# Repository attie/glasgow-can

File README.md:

# Glasgow CAN Interface Addon

This repository provides the hardware and software components of a CAN Interface Add-On for the [Glasgow Digital Interface Explorer](https://github.com/GlasgowEmbedded/glasgow).

A rough spec is outlined below:

- Sits alongside a Glasgow board
- 2x CAN interfaces, available on a single port
- Standard DE-9 connectors
  - Default pinout is suitable for use with existing CAN and OBD-II adapter cables (on CAN1 and CAN2 repsectively)
  - Can be easily rewired by cutting jumpers
- Spring-loaded terminal blocks for ease-of-use
- Indicator LEDs for Tx and Rx
- Software configurable 120Ω termination, with state LED
- ESD protection
- CAN FD support in hardware (software to follow)

Future plans:

- Isolation between each CAN port and the Glasgow (and host)

Out-of-Tree support will be required when work on the applet begins (see PR [#213](https://github.com/GlasgowEmbedded/glasgow/pull/213)).

---

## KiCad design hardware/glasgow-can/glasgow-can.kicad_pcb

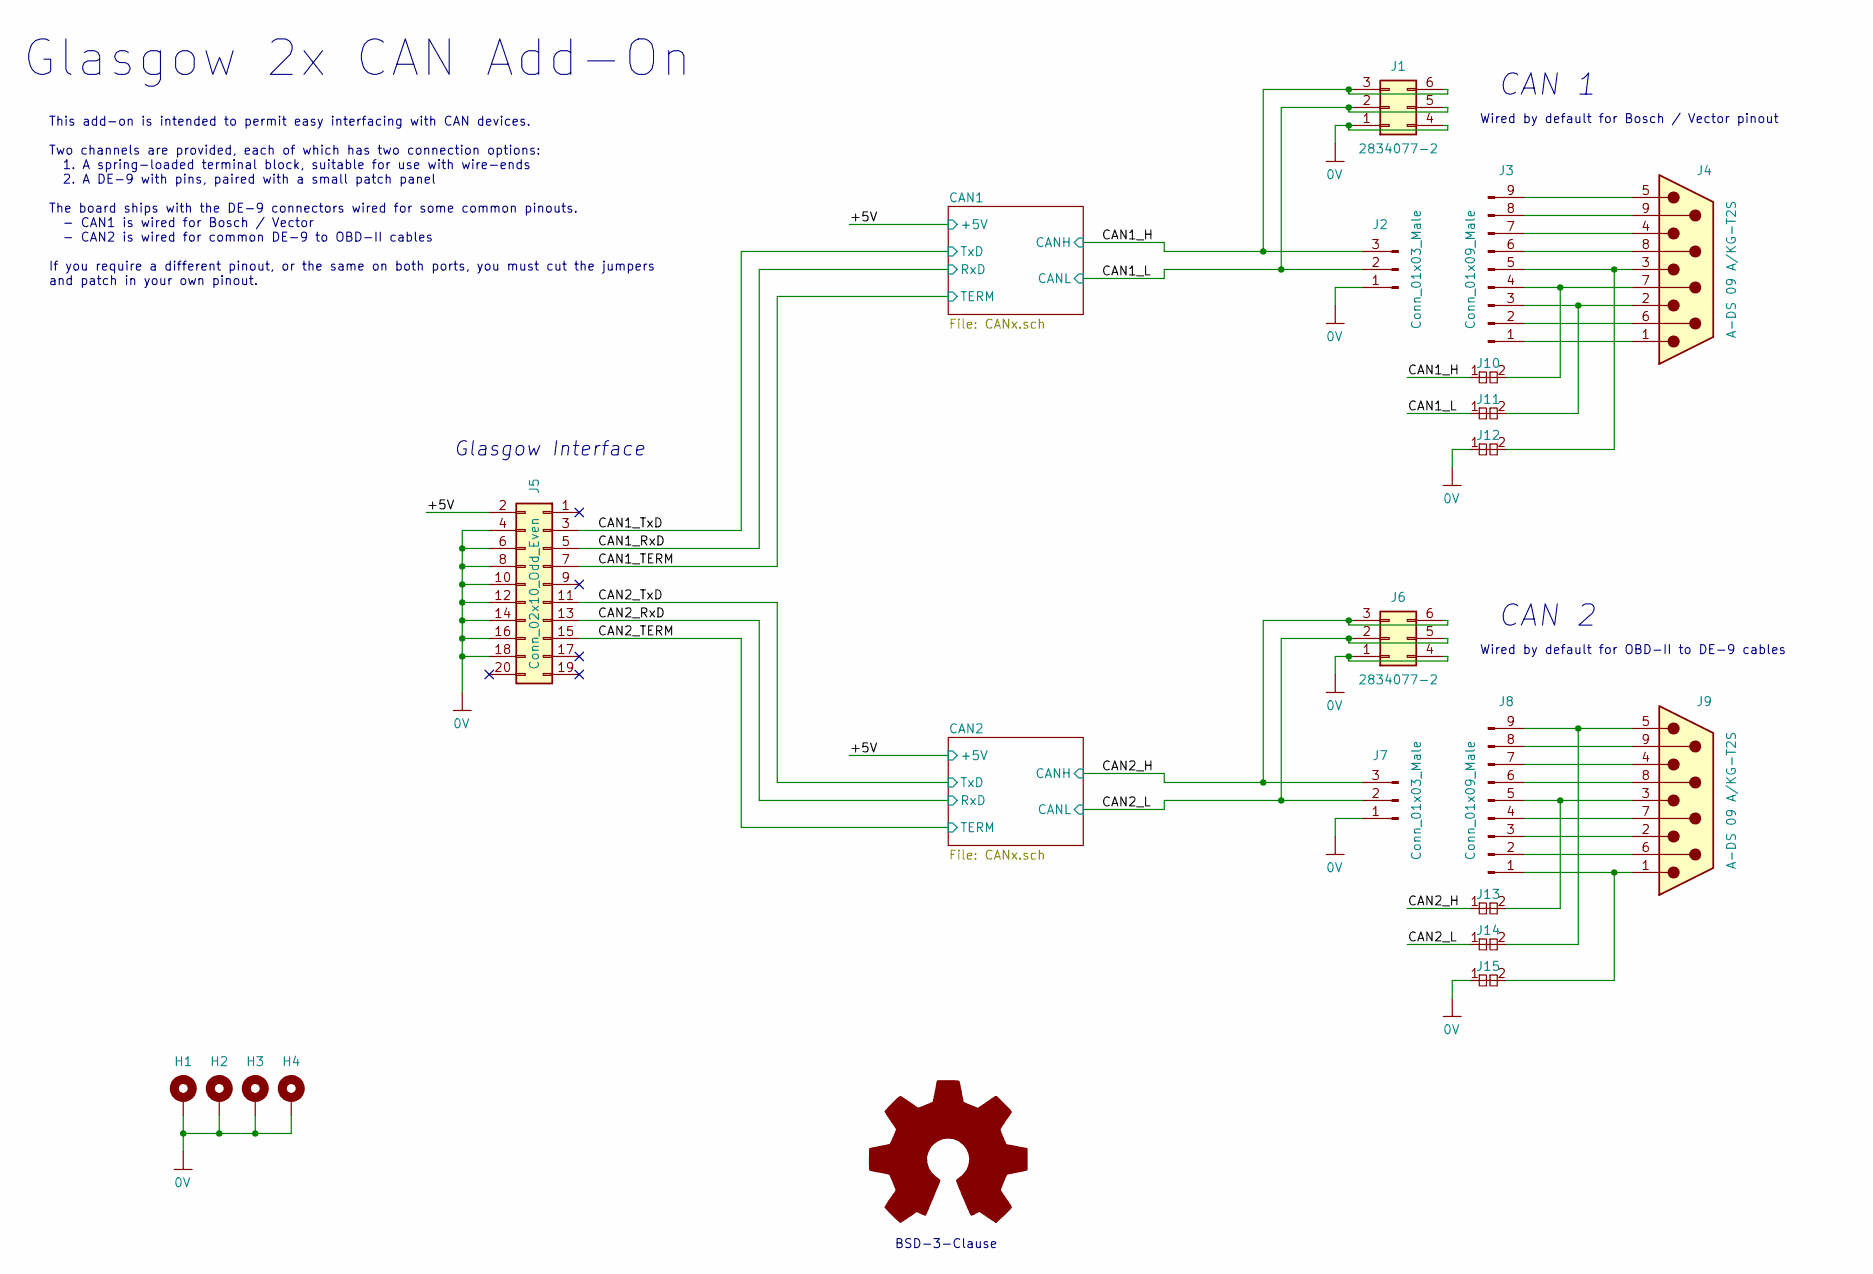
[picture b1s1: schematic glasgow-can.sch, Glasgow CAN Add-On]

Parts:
H1, H2, H3, H4: MountingHole_Pad; MountingHole_3.2mm_M3_Pad_Via
J1, J6: 2834077-2; TE_2834077-2; MPN 2834077-2
J2, J7: Conn_01x03_Male; PinHeader_1x03_P2.54mm_Vertical
J3, J8: Conn_01x09_Male; PinHeader_1x09_P2.54mm_Vertical
J4, J9: A-DS 09 A/KG-T2S; DSUB-9_Male_Horizontal_P2.77x2.84mm_EdgePinOffset7.70mm_Hou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; MPN A-DS 09 A/KG-T2S
J5: Conn_02x10_Odd_Even; IDC-Header_2x10_P2.54mm_Vertical
J10, J11, J12, J13, J14, J15: pkl_jumper_nc; J_NC_0603_20
LOGO1: Logo_Open_Hardware_Large; OSHW-Logo2_7.3x6mm_SilkScreen

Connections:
0V: H1.1, H2.1, H3.1, H4.1, J1.1, J1.4, J2.1, J5.4, J5.6, J5.8, J5.10, J5.12, J5.14, J5.16, J5.18, J6.1, J6.4, J7.1, J12.1, J15.1; also elsewhere on the board
/+5V: J5.2; also elsewhere on the board
/CAN1_H: J1.3, J1.6, J2.3, J10.1; also elsewhere on the board
/CAN1_L: J1.2, J1.5, J2.2, J11.1; also elsewhere on the board
/CAN1_RxD: J5.5; also elsewhere on the board
/CAN1_TERM: J5.7; also elsewhere on the board
/CAN1_TxD: J5.3; also elsewhere on the board
/CAN2_H: J6.3, J6.6, J7.3, J13.1; also elsewhere on the board
/CAN2_L: J6.2, J6.5, J7.2, J14.1; also elsewhere on the board
/CAN2_RxD: J5.13; also elsewhere on the board
/CAN2_TERM: J5.15; also elsewhere on the board
/CAN2_TxD: J5.11; also elsewhere on the board
unnamed: J3.1, J4.1
unnamed: J3.2, J4.6
unnamed: J3.6, J4.8
unnamed: J3.7, J4.4
unnamed: J3.8, J4.9
unnamed: J3.9, J4.5
unnamed: J8.2, J9.6
unnamed: J8.3, J9.2
unnamed: J8.4, J9.7
unnamed: J8.6, J9.8
unnamed: J8.7, J9.4
unnamed: J8.8, J9.9
unnamed: J3.4, J4.7, J10.2
unnamed: J3.3, J4.2, J11.2
unnamed: J3.5, J4.3, J12.2
unnamed: J8.5, J9.3, J13.2
unnamed: J8.9, J9.5, J14.2
unnamed: J8.1, J9.1, J15.2

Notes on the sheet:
Glasgow Interface
This add-on is intended to permit easy interfacing with CAN devices. Two channels are provided, each of which has two connection options: 1. A spring-loaded terminal block, suitable for use with wire-ends 2. A DE-9 with pins, paired with a small patch panel The board ships with the DE-9 connectors 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
CAN 1
CAN 2
Wired by default for Bosch / Vector pinout
Wired by default for OBD-II to DE-9 cables
Glasgow 2x CAN Add-On
BSD-3-Clause

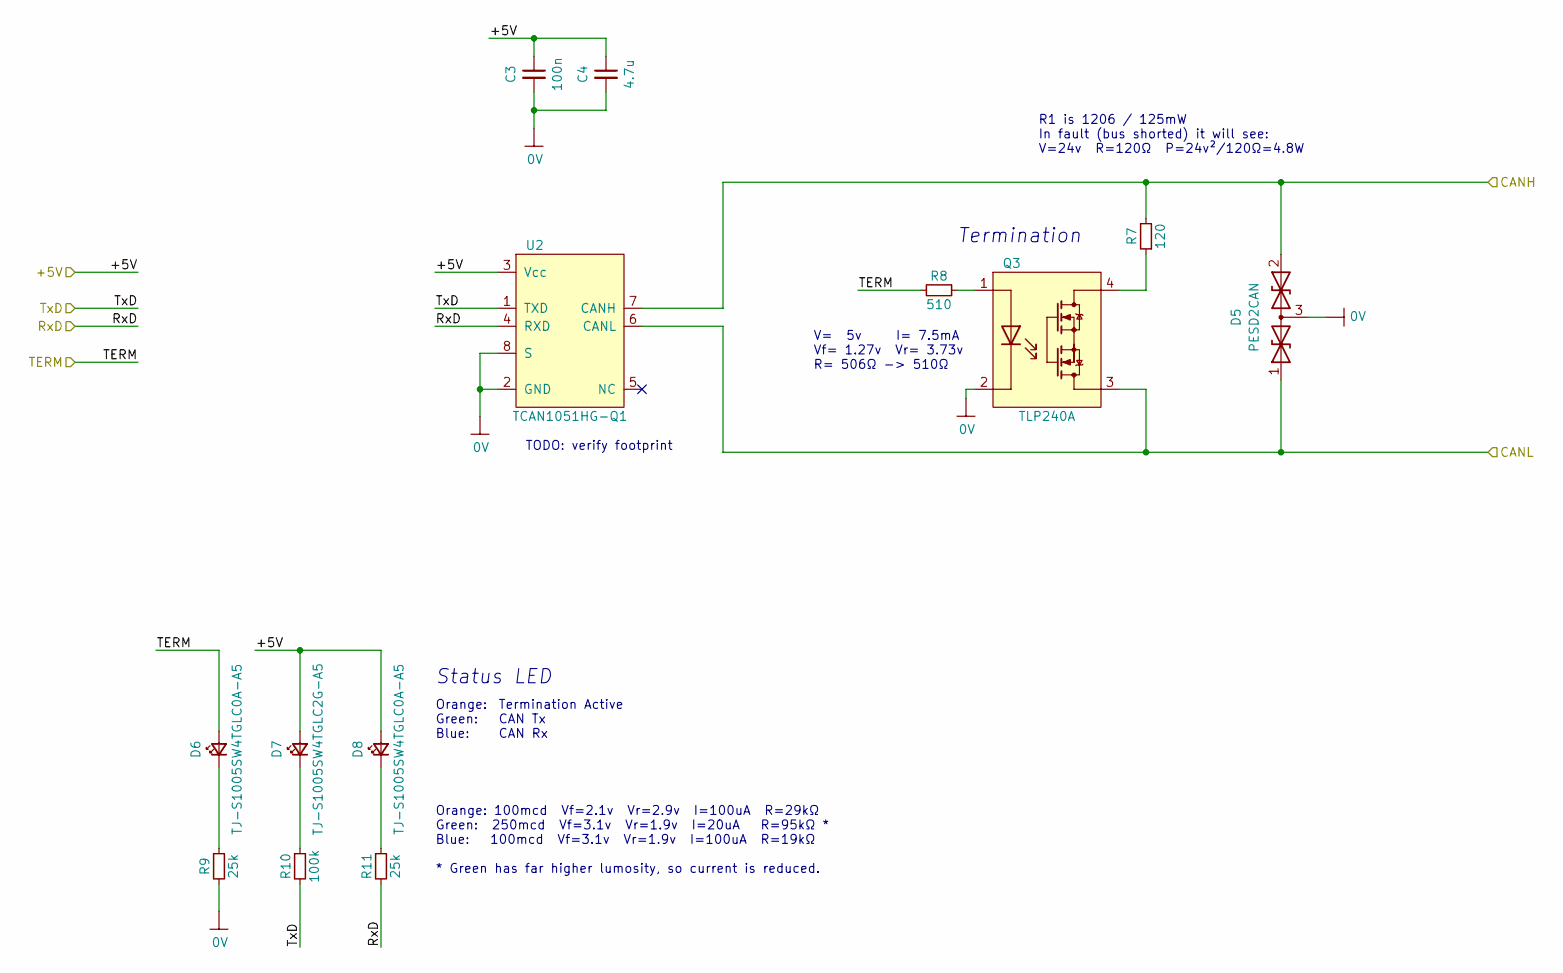
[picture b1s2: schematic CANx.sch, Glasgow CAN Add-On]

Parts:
C1: 100n; C_0402_1005Metric
C2: 4.7u; C_0603_1608Metric
D1: PESD2CAN; SOT-23; MPN PESD2CAN
D2, D4: TJ-S1005SW4TGLC0A-A5; LED_0402_1005Metric_Pad0.77x0.64mm_HandSolder; MPN TJ-S1005SW4TGLC0A-A5
D3: TJ-S1005SW4TGLC2G-A5; LED_0402_1005Metric_Pad0.77x0.64mm_HandSolder; MPN TJ-S1005SW4TGLC2G-A5
Q1: TLP240A; TLP240A_5; MPN TLP240A(TP1,F
R1: 120; R_1206_3216Metric
R2: 510; R_0402_1005Metric
R3, R5: 25k; R_0402_1005Metric
R4: 100k; R_0402_1005Metric
U1: TCAN1051; DFN-8-1EP_3x3mm_P0.65mm_EP1.7x2.05mm; MPN TCAN1051HG-Q1

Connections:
0V: C1.2, C2.2, D1.3 (common), Q1.2, R3.2, U1.2 (GND), U1.8 (S); also elsewhere on the board
/+5V: C1.1, C2.1, D3.2 (A), D4.2 (A), U1.3 (Vcc); also elsewhere on the board
/CAN1_H: D1.2 (A2), R1.2, U1.7 (CANH); also elsewhere on the board
/CAN1_L: D1.1 (A1), Q1.3, U1.6 (CANL); also elsewhere on the board
/CAN1_RxD: R5.2, U1.4 (RXD); also elsewhere on the board
/CAN1_TERM: D2.2 (A), R2.2; also elsewhere on the board
/CAN1_TxD: R4.2, U1.1 (TXD); also elsewhere on the board
unnamed: D2.1 (K), R3.1
unnamed: D3.1 (K), R4.1
unnamed: D4.1 (K), R5.1
unnamed: Q1.1, R2.1
unnamed: Q1.4, R1.1

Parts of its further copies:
C3: 100n; C_0402_1005Metric
C4: 4.7u; C_0603_1608Metric
D5: PESD2CAN; SOT-23; MPN PESD2CAN
D6, D8: TJ-S1005SW4TGLC0A-A5; LED_0402_1005Metric_Pad0.77x0.64mm_HandSolder; MPN TJ-S1005SW4TGLC0A-A5
D7: TJ-S1005SW4TGLC2G-A5; LED_0402_1005Metric_Pad0.77x0.64mm_HandSolder; MPN TJ-S1005SW4TGLC2G-A5
Q3: TLP240A; TLP240A_5; MPN TLP240A(TP1,F
R7: 120; R_1206_3216Metric
R8: 510; R_0402_1005Metric
R9, R11: 25k; R_0402_1005Metric
R10: 100k; R_0402_1005Metric
U2: TCAN1051; DFN-8-1EP_3x3mm_P0.65mm_EP1.7x2.05mm; MPN TCAN1051HG-Q1

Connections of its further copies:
0V: C3.2, C4.2, D5.3 (common), Q3.2, R9.2, U2.2 (GND), U2.8 (S); also elsewhere on the board
/+5V: C3.1, C4.1, D7.2 (A), D8.2 (A), U2.3 (Vcc); also elsewhere on the board
/CAN2_H: D5.2 (A2), R7.2, U2.7 (CANH); also elsewhere on the board
/CAN2_L: D5.1 (A1), Q3.3, U2.6 (CANL); also elsewhere on the board
/CAN2_RxD: R11.2, U2.4 (RXD); also elsewhere on the board
/CAN2_TERM: D6.2 (A), R8.2; also elsewhere on the board
/CAN2_TxD: R10.2, U2.1 (TXD); also elsewhere on the board
unnamed: D6.1 (K), R9.1
unnamed: D7.1 (K), R10.1
unnamed: D8.1 (K), R11.1
unnamed: Q3.1, R8.1
unnamed: Q3.4, R7.1

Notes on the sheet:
V= 5v I= 7.5mA Vf= 1.27v Vr= 3.73v R= 506Ω -> 510Ω
Orange: 100mcd Vf=2.1v Vr=2.9v I=100uA R=29kΩ Green: 250mcd Vf=3.1v Vr=1.9v I=20uA R=95kΩ * Blue: 100mcd Vf=3.1v Vr=1.9v I=100uA R=19kΩ * Green has far higher lumosity, so current is reduced.
R1 is 1206 / 125mW In fault (bus shorted) it will see: V=24v R=120Ω P=24v²/120Ω=4.8W
TODO: verify footprint
Termination
Orange: Green: Blue:
Status LED
Termination Active CAN Tx CAN Rx

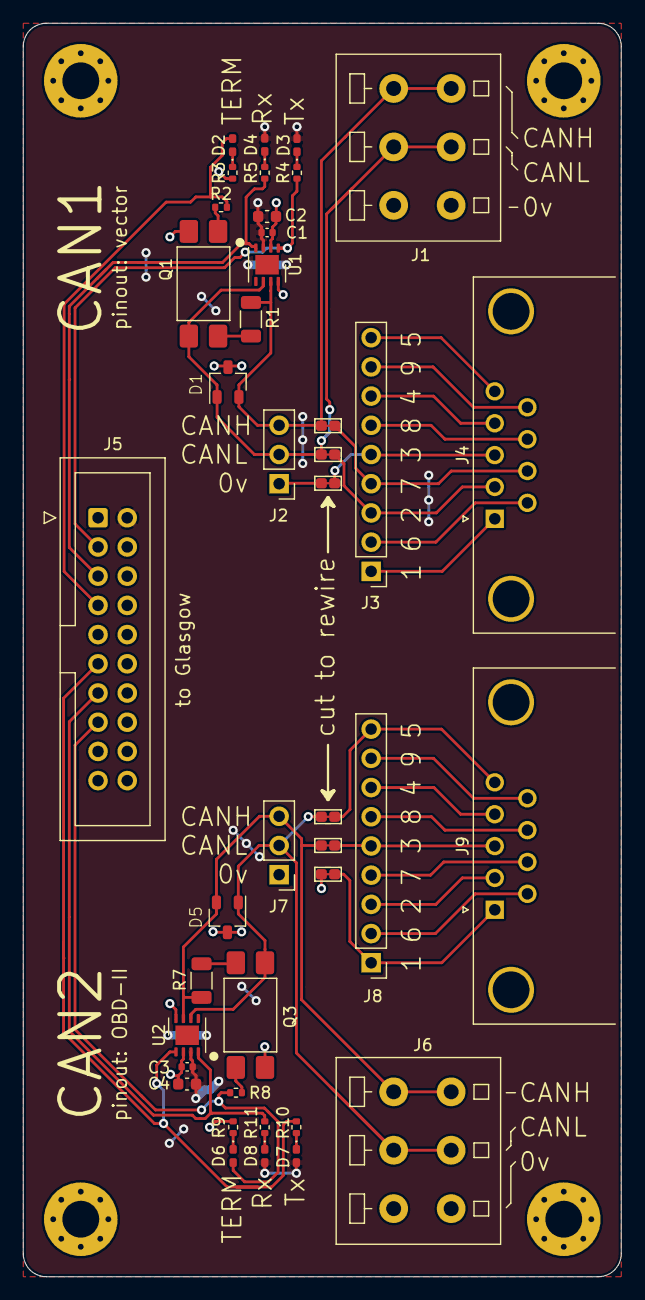
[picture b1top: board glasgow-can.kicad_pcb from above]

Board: 2 copper layers, 52.0 x 109.0 mm, 46 parts (1 on the bottom side), 40 nets.

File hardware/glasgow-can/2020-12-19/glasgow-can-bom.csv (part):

"Source:","Z:\proj\glasgow-can\attie\hardware\glasgow-can\glasgow-can.sch"
"Date:","20/12/2020 12:08:45 AM"
"Tool:","Eeschema (5.1.8)-1"
"Generator:","C:\Program Files\KiCad\bin\scripting\plugins/bom_csv_grouped_by_value.py"
"Component Count:","46"

"Individual Components:"

"Item","Qty","Reference(s)","Value","LibPart","Footprint","Datasheet","MFG","MFR","MPN"
"","","C1","100n","Device:C_Small","Capacitor_SMD:C_0402_1005Metric","~","","",""
"","","C2","4.7u","Device:C_Small","Capacitor_SMD:C_0603_1608Metric","~","","",""
"","","C3","100n","Device:C_Small","Capacitor_SMD:C_0402_1005Metric","~","","",""
"","","C4","4.7u","Device:C_Small","Capacitor_SMD:C_0603_1608Metric","~","","",""
"","","D1","PESD2CAN","Device:D_TVS_x2_AAC","rhais_package-smd:SOT-23","~","","Nexperia","PESD2CAN"
"","","D2","TJ-S1005SW4TGLC0A-A5","Device:LED_Small","LED_SMD:LED_0402_1005Metric_Pad0.77x0.64mm_HandSolder","~","","TOGIALED","TJ-S1005SW4TGLC0A-A5"
"","","D3","TJ-S1005SW4TGLC2G-A5","Device:LED_Small","LED_SMD:LED_0402_1005Metric_Pad0.77x0.64mm_HandSolder","~","","TOGIALED","TJ-S1005SW4TGLC2G-A5"
"","","D4","TJ-S1005SW4TGLC0A-A5","Device:LED_Small","LED_SMD:LED_0402_1005Metric_Pad0.77x0.64mm_HandSolder","~","","TOGIALED","TJ-S1005SW4TGLC0A-A5"
"","","D5","PESD2CAN","Device:D_TVS_x2_AAC","rhais_package-smd:SOT-23","~","","Nexperia","PESD2CAN"
"","","D6","TJ-S1005SW4TGLC0A-A5","Device:LED_Small","LED_SMD:LED_0402_1005Metric_Pad0.77x0.64mm_HandSolder","~","","TOGIALED","TJ-S1005SW4TGLC0A-A5"
"","","D7","TJ-S1005SW4TGLC2G-A5","Device:LED_Small","LED_SMD:LED_0402_1005Metric_Pad0.77x0.64mm_HandSolder","~","","TOGIALED","TJ-S1005SW4TGLC2G-A5"
"","","D8","TJ-S1005SW4TGLC0A-A5","Device:LED_Small","LED_SMD:LED_0402_1005Metric_Pad0.77x0.64mm_HandSolder","~","","TOGIALED","TJ-S1005SW4TGLC0A-A5"
"","","H1","MountingHole_Pad","Mechanical:MountingHole_Pad","MountingHole:MountingHole_3.2mm_M3_Pad_Via","~","","",""
"","","H2","MountingHole_Pad","Mechanical:MountingHole_Pad","MountingHole:MountingHole_3.2mm_M3_Pad_Via","~","","",""
"","","H3","MountingHole_Pad","Mechanical:MountingHole_Pad","MountingHole:MountingHole_3.2mm_M3_Pad_Via","~","","",""
"","","H4","MountingHole_Pad","Mechanical:MountingHole_Pad","MountingHole:MountingHole_3.2mm_M3_Pad_Via","~","","",""
"","","J1","2834077-2","Connector_Generic:Conn_02x03_Top_Bottom","glasgow-can:TE_2834077-2","~","TE Connectivity","","2834077-2"
"","","J2","Conn_01x03_Male","Connector:Conn_01x03_Male","Connector_PinHeader_2.54mm:PinHeader_1x03_P2.54mm_Vertical","~","","",""
"","","J3","Conn_01x09_Male","Connector:Conn_01x09_Male","Connector_PinHeader_2.54mm:PinHeader_1x09_P2.54mm_Vertical","~","","",""
"","","J4","A-DS 09 A/KG-T2S","Connector:DB9_Male","Connector_Dsub:DSUB-9_Male_Horizontal_P2.77x2.84mm_EdgePinOffset7.70mm_Housed_MountingHolesOffset9.12mm"," ~","","Assmann WSW Components","A-DS 09 A/KG-T2S"
"","","J5","Conn_02x10_Odd_Even","Connector_Generic:Conn_02x10_Odd_Even","Connector_IDC:IDC-Header_2x10_P2.54mm_Vertical","~","","",""
"","","J6","2834077-2","Connector_Generic:Conn_02x03_Top_Bottom","glasgow-can:TE_2834077-2","~","TE Connectivity","","2834077-2"
"","","J7","Conn_01x03_Male","Connector:Conn_01x03_Male","Connector_PinHeader_2.54mm:PinHeader_1x03_P2.54mm_Vertical","~","","",""
"","","J8","Conn_01x09_Male","Connector:Conn_01x09_Male","Connector_PinHeader_2.54mm:PinHeader_1x09_P2.54mm_Vertical","~","","",""
"","","J9","A-DS 09 A/KG-T2S","Connector:DB9_Male","Connector_Dsub:DSUB-9_Male_Horizontal_P2.77x2.84mm_EdgePinOffset7.70mm_Housed_MountingHolesOffset9.12mm"," ~","","Assmann WSW Components","A-DS 09 A/KG-T2S"
"","","J10","pkl_jumper_nc","pkl_misc:pkl_jumper_nc","pkl_jumpers:J_NC_0603_20","","","",""
"","","J11","pkl_jumper_nc","pkl_misc:pkl_jumper_nc","pkl_jumpers:J_NC_0603_20","","","",""
"","","J12","pkl_jumper_nc","pkl_misc:pkl_jumper_nc","pkl_jumpers:J_NC_0603_20","","","",""
"","","J13","pkl_jumper_nc","pkl_misc:pkl_jumper_nc","pkl_jumpers:J_NC_0603_20","","","",""
"","","J14","pkl_jumper_nc","pkl_misc:pkl_jumper_nc","pkl_jumpers:J_NC_0603_20","","","",""
"","","J15","pkl_jumper_nc","pkl_misc:pkl_jumper_nc","pkl_jumpers:J_NC_0603_20","","","",""
"","","LOGO1","Logo_Open_Hardware_Large","Graphic:Logo_Open_Hardware_Large","Symbol:OSHW-Logo2_7.3x6mm_SilkScreen","~","","",""
"","","Q1","TLP240A","glasgow-can:TLP240A","glasgow-can:TLP240A_5","","","Toshiba","TLP240A(TP1,F"
"","","Q3","TLP240A","glasgow-can:TLP240A","glasgow-can:TLP240A_5","","","Toshiba","TLP240A(TP1,F"
"","","R1","120","Device:R_Small","Resistor_SMD:R_1206_3216Metric","~","","",""
"","","R2","510","Device:R_Small","Resistor_SMD:R_0402_1005Metric","~","","",""
"","","R3","25k","Device:R_Small","Resistor_SMD:R_0402_1005Metric","~","","",""
"","","R4","100k","Device:R_Small","Resistor_SMD:R_0402_1005Metric","~","","",""
"","","R5","25k","Device:R_Small","Resistor_SMD:R_0402_1005Metric","~","","",""
"","","R7","120","Device:R_Small","Resistor_SMD:R_1206_3216Metric","~","","",""
"","","R8","510","Device:R_Small","Resistor_SMD:R_0402_1005Metric","~","","",""
"","","R9","25k","Device:R_Small","Resistor_SMD:R_0402_1005Metric","~","","",""
"","","R10","100k","Device:R_Small","Resistor_SMD:R_0402_1005Metric","~","","",""
"","","R11","25k","Device:R_Small","Resistor_SMD:R_0402_1005Metric","~","","",""
"","","U1","TCAN1051","glasgow-can:TCAN1051","Package_DFN_QFN:DFN-8-1EP_3x3mm_P0.65mm_EP1.7x2.05mm","","","Texas Instruments","TCAN1051HG-Q1"
"","","U2","TCAN1051","glasgow-can:TCAN1051","Package_DFN_QFN:DFN-8-1EP_3x3mm_P0.65mm_EP1.7x2.05mm","","","Texas Instruments","TCAN1051HG-Q1"



"Collated Components:"

"Item","Qty","Reference(s)","Value","LibPart","Footprint","Datasheet","MFG","MFR","MPN"
"1","2","C1, C3","100n","Device:C_Small","Capacitor_SMD:C_0402_1005Metric","~","","",""
"2","2","C2, C4","4.7u","Device:C_Small","Capacitor_SMD:C_0603_1608Metric","~","","",""
"3","2","D1, D5","PESD2CAN","Device:D_TVS_x2_AAC","rhais_package-smd:SOT-23","~","","Nexperia","PESD2CAN"
"4","4","D2, D4, D6, D8","TJ-S1005SW4TGLC0A-A5","Device:LED_Small","LED_SMD:LED_0402_1005Metric_Pad0.77x0.64mm_HandSolder","~","","TOGIALED","TJ-S1005SW4TGLC0A-A5"
"5","2","D3, D7","TJ-S1005SW4TGLC2G-A5","Device:LED_Small","LED_SMD:LED_0402_1005Metric_Pad0.77x0.64mm_HandSolder","~","","TOGIALED","TJ-S1005SW4TGLC2G-A5"
"6","4","H1, H2, H3, H4","MountingHole_Pad","Mechanical:MountingHole_Pad","MountingHole:MountingHole_3.2mm_M3_Pad_Via","~","","",""
"7","2","J1, J6","2834077-2","Connector_Generic:Conn_02x03_Top_Bottom","glasgow-can:TE_2834077-2","~","TE Connectivity","","2834077-2"
"8","2","J2, J7","Conn_01x03_Male","Connector:Conn_01x03_Male","Connector_PinHeader_2.54mm:PinHeader_1x03_P2.54mm_Vertical","~","","",""
"9","2","J3, J8","Conn_01x09_Male","Connector:Conn_01x09_Male","Connector_PinHeader_2.54mm:PinHeader_1x09_P2.54mm_Vertical","~","","",""
"10","2","J4, J9","A-DS 09 A/KG-T2S","Connector:DB9_Male","Connector_Dsub:DSUB-9_Male_Horizontal_P2.77x2.84mm_EdgePinOffset7.70mm_Housed_MountingHolesOffset9.12mm"," ~","","Assmann WSW Components","A-DS 09 A/KG-T2S"
"11","1","J5","Conn_02x10_Odd_Even","Connector_Generic:Conn_02x10_Odd_Even","Connector_IDC:IDC-Header_2x10_P2.54mm_Vertical","~","","",""
"12","6","J10, J11, J12, J13, J14, J15","pkl_jumper_nc","pkl_misc:pkl_jumper_nc","pkl_jumpers:J_NC_0603_20","","","",""
"13","1","LOGO1","Logo_Open_Hardware_Large","Graphic:Logo_Open_Hardware_Large","Symbol:OSHW-Logo2_7.3x6mm_SilkScreen","~","","",""
"14","2","Q1, Q3","TLP240A","glasgow-can:TLP240A","glasgow-can:TLP240A_5","","","Toshiba","TLP240A(TP1,F"
"15","2","R1, R7","120","Device:R_Small","Resistor_SMD:R_1206_3216Metric","~","","",""
"16","2","R2, R8","510","Device:R_Small","Resistor_SMD:R_0402_1005Metric","~","","",""
"17","4","R3, R5, R9, R11","25k","Device:R_Small","Resistor_SMD:R_0402_1005Metric","~","","",""
"18","2","R4, R10","100k","Device:R_Small","Resistor_SMD:R_0402_1005Metric","~","","",""
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
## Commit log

2020-10-16 initial outline / spec
2020-10-16 add termination requirement
2020-10-16 add ESD requirement and pinout
2020-10-16 move isolation to future plans
2020-11-19 schematic and rough layout
2020-11-21 tidy up schematics
2020-11-21 add gitignore
2020-11-21 add note about pinouts via CANtact / Linklayer wiki
2020-12-03 schematic revised according to discussion in #1, and layout mostly complete... some TODOs remain
2020-12-04 fix DE-9 footprint, spruce up schematic and layout
2020-12-04 remove fp-info-cache
2020-12-04 add license
2020-12-04 fixup README, and other misc changes
2020-12-04 fixup ohm symbol
2020-12-04 regenerate images, and add to README
2020-12-04 remove incorrect/stale pinout image
2020-12-04 remove stray trace
2020-12-19 minor tweaks
2020-12-20 add manufacturing data for rev0 / 2020-12-19
2021-01-06 tweak LEDs for availability, and revise CAN line driver part number
